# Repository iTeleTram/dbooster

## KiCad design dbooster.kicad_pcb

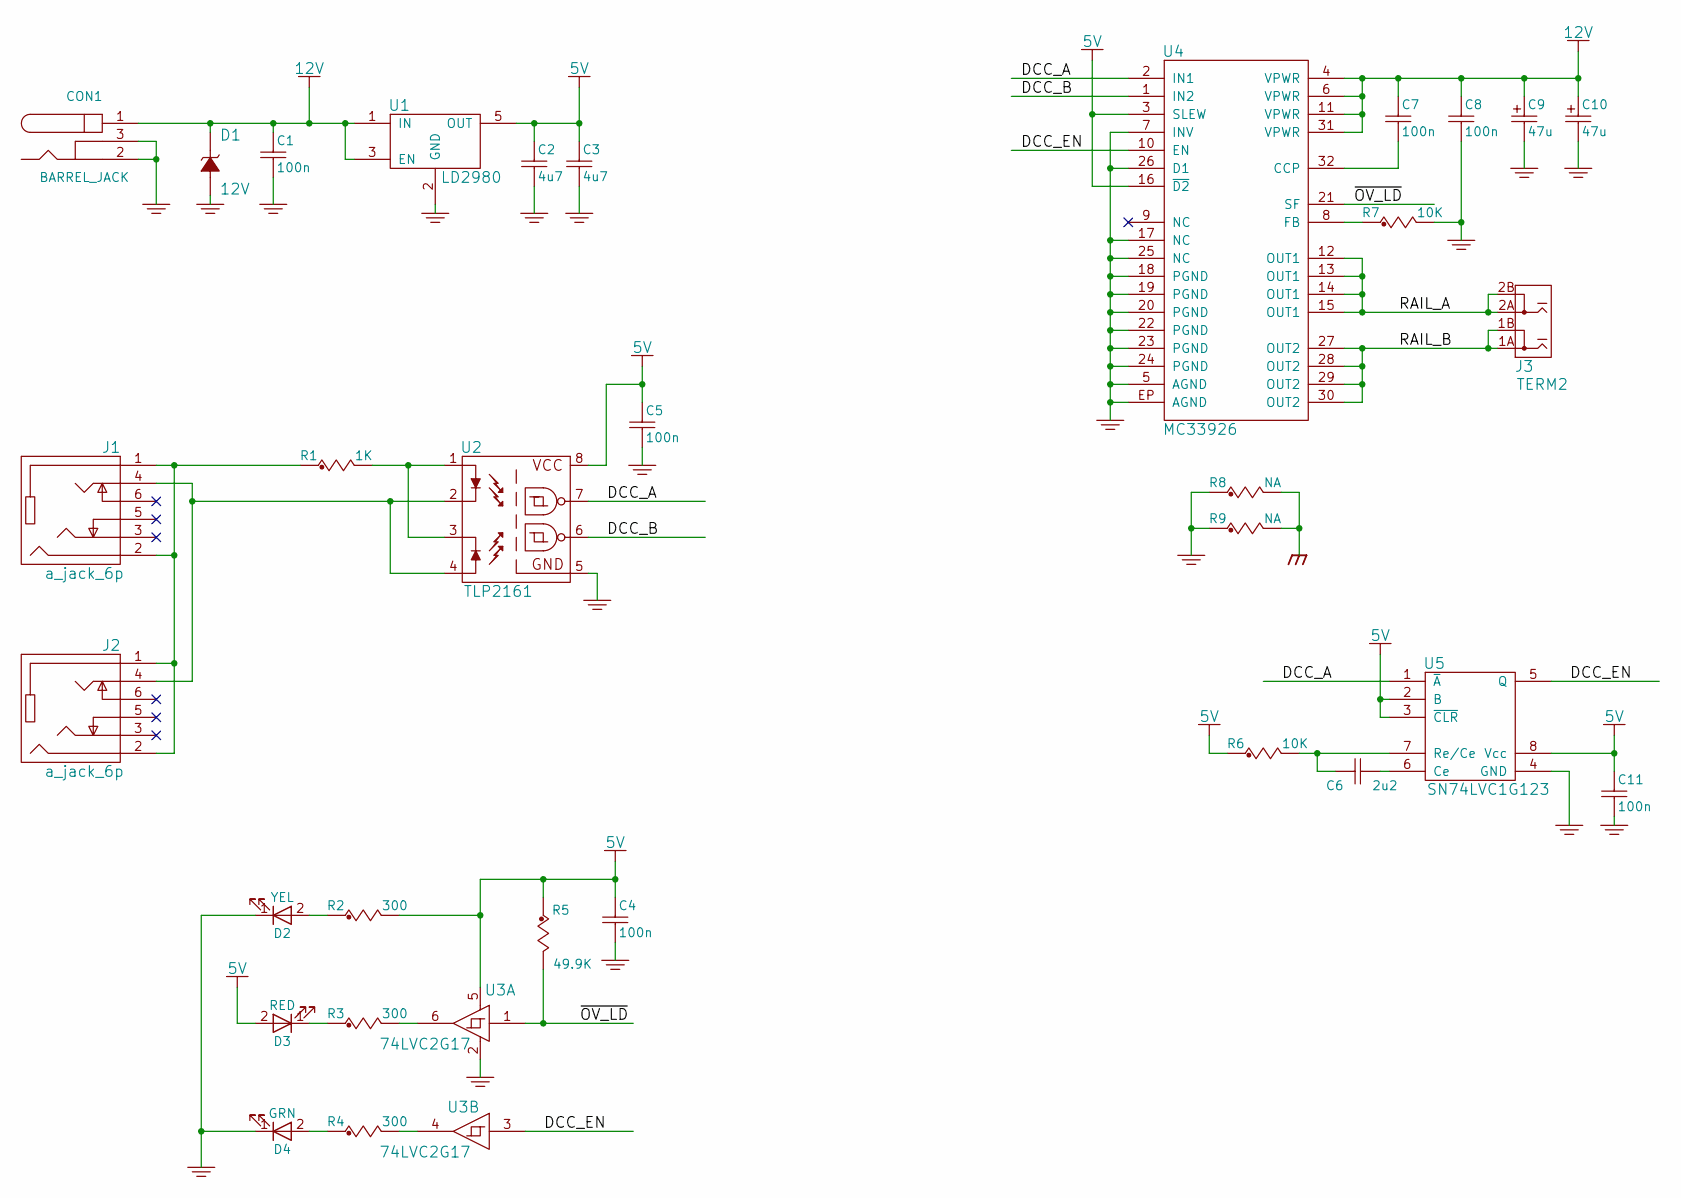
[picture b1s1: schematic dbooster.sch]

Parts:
C1: 100n; C_0603; Voltage CC0603KRX5R6BB105; mfg_pn 06035C104KAT2A
C2, C3: 4u7; C_0603; Voltage 6.3V; mfg_pn GRM188R60J475KE19J
C4, C5, C7, C8, C11: 100n; C_0603; Voltage 50V; mfg_pn 06035C104KAT2A
C6: 2u2; C_0603; Voltage 16V; mfg_pn C0603C225K4PACTU
C9, C10: 47u; CP_Elec_6.3x5.8; Voltage 25V; mfg_pn EMZJ250ADA470MF61G
CON1: BARREL_JACK; pjack_smt; mfg_pn PJ-002AH-SMT-TR
D1: 12V; D_SMB_Standard; mfg_pn SMBJ10D-M3/H
D2: YEL; LED_D3.0mm_FlatTop; mfg_pn WP710A10YT
D3: RED; LED_D3.0mm_FlatTop; mfg_pn WP710A10IT
D4: GRN; LED_D3.0mm_FlatTop; mfg_pn WP710A10GT
J1, J2: a_jack_6p; ajack_smt_6
J3: TERM2; pterm_2; mfg_pn 1770885
R1: 1K; R_0603; mfg_pn CRCW06031K00FKEA
R2, R3, R4: 300; R_0603; mfg_pn RC0603FR-07300RL
R5: 49.9K; R_0603; mfg_pn CRCW060349K9FKEA
R6, R7: 10K; R_0603; mfg_pn CRCW060310K0FKEA
R8, R9: NA; R_0603
U1: LD2980; SOT-23-5; mfg_pn LD2980CM50TR
U2: TLP2161; SOIC-8_3.9x4.9mm_Pitch1.27mm; mfg_pn TLP2161(F)
U3: 74LVC2G17; SOT-23-6; mfg_pn SN74LVC2G17DBVR
U4: MC33926; pwr_qfn_8x8_32; mfg_pn MC33926PNB
U5: SN74LVC1G123; TSSOP-8_3x3mm_Pitch0.65mm; mfg_pn 74LVC1G123DCT

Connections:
5V: C2.2, C3.2, C4.2, C5.2, C11.2, D3.2 (A), R2.2, R5.1, R6.1, U1.5 (OUT), U2.8 (VCC), U3.5 (VCC), U4.3 (SLEW), U4.16 (~D2), U5.2 (B), U5.3 (~CLR), U5.8 (Vcc)
12V: C1.2, C7.2, C8.2, C9.1, C10.1, CON1.1, D1.1 (C), U1.1 (IN), U1.3 (EN), U4.4 (VPWR), U4.6 (VPWR), U4.11 (VPWR), U4.31 (VPWR)
/DCC_A: U2.7 (OUT1), U4.2 (IN1), U5.1 (~A)
/DCC_B: U2.6 (OUT2), U4.1 (IN2)
/DCC_EN: U3.3 (IN2), U4.10 (EN), U5.5 (Q)
/RAIL_A: J3.2A (2), J3.2B (2), U4.12 (OUT1), U4.13 (OUT1), U4.14 (OUT1), U4.15 (OUT1)
/RAIL_B: J3.1A (1), J3.1B (1), U4.27 (OUT2), U4.28 (OUT2), U4.29 (OUT2), U4.30 (OUT2)
/~OV_LD: R5.2, U3.1 (IN2), U4.21 (SF)
GND: C1.1, C2.1, C3.1, C4.1, C5.1, C8.1, C9.2, C10.2, C11.1, CON1.2, CON1.3, D1.2 (A), D2.1 (K), D4.1 (K), R7.2, R8.1, R9.1, U1.2 (GND), U2.5 (GND), U3.2 (GND), U4.5 (AGND), U4.7 (INV), U4.17 (NC), U4.18 (PGND), U4.19 (PGND), U4.20 (PGND), U4.22 (PGND), U4.23 (PGND), U4.24 (PGND), U4.25 (NC), U4.26 (D1), U4.EP (AGND), U5.4 (GND)
GNDPWR: R8.2, R9.2
unnamed: C6.1, U5.6 (Ce)
unnamed: C6.2, R6.2, U5.7 (Re/Ce)
unnamed: C7.1, U4.32 (CCP)
unnamed: D2.2 (A), R2.1
unnamed: D3.1 (K), R3.1
unnamed: D4.2 (A), R4.1
unnamed: J1.1, J1.2, J2.1, J2.2, R1.1
unnamed: J1.4, J2.4, U2.2 (C1), U2.4 (A2)
unnamed: R1.2, U2.1 (A1), U2.3 (C2)
unnamed: R3.2, U3.6 (OUT2)
unnamed: R4.2, U3.4 (OUT2)
unnamed: R7.1, U4.8 (FB)

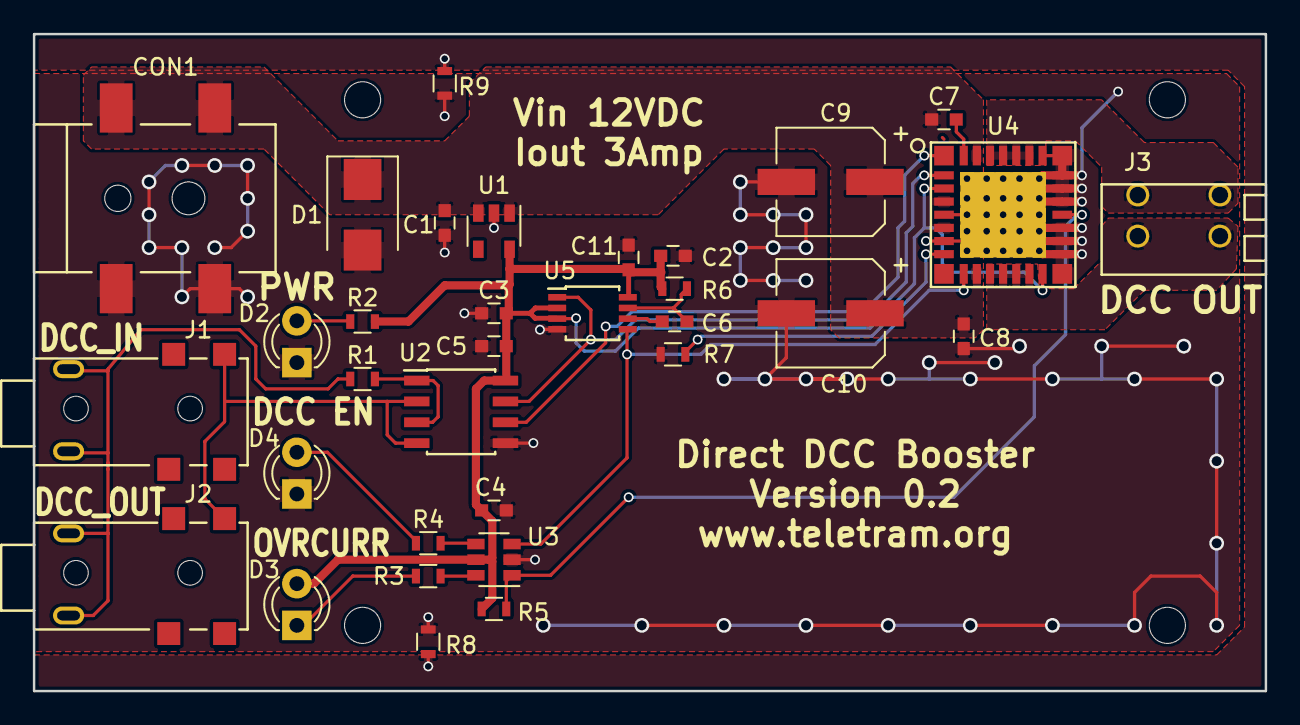
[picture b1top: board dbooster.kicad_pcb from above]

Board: 2 copper layers, 75.0 x 40.0 mm, 33 parts (0 on the bottom side), 22 nets.
